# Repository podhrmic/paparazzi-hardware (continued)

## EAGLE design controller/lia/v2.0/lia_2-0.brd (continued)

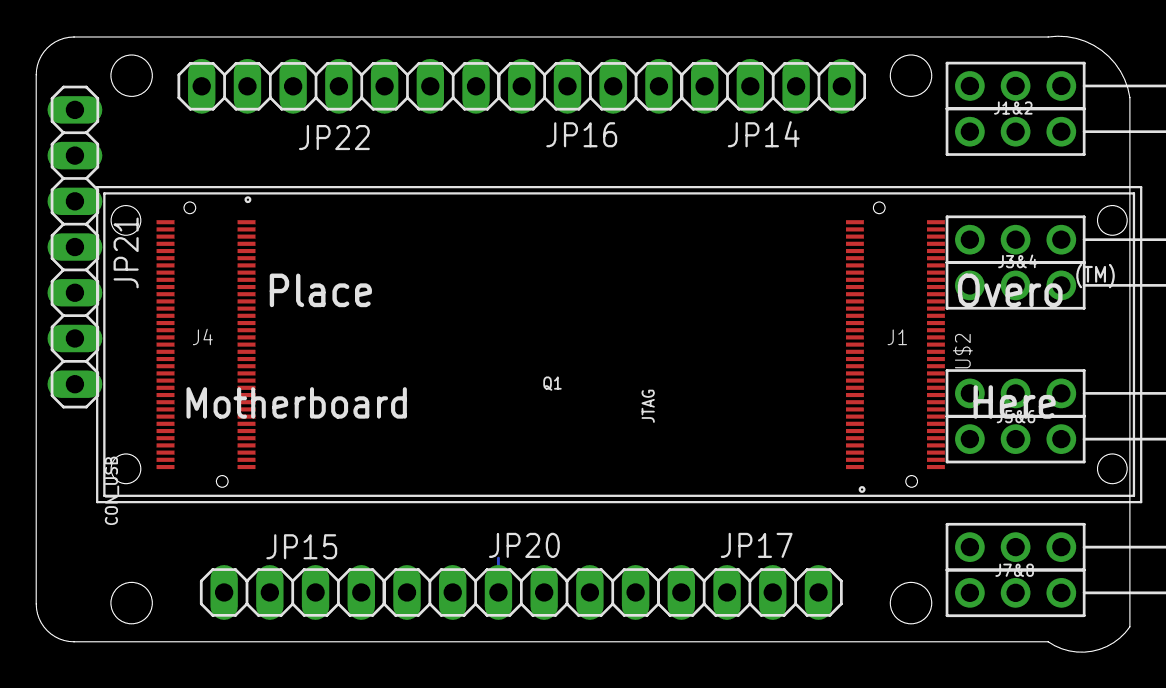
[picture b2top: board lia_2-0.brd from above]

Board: 2 copper layers, 60.8 x 34.2 mm, 16 parts (0 on the bottom side), 3 nets.

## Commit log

2015-11-30 Lisa breakout board
2016-09-18 Updated aspirin v2.2 to r1
2016-09-18 Updated led footprints to have placement information about orientation.
2016-09-18 Added prototype of connector shield Lisa/S with Walkera Genius CPv2
2016-09-18 Updated gerber generation files.
2016-09-18 SD Logger for Lisa/S
2016-09-18 Updated V2.1 Lisa/M(X) hardware to the final production version.
